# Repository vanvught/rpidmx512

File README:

Raspberry Pi DMX512 / RDM / MIMI / OSC / ArtNet-3 / Pixel
=======

*. RDM Controller with USB [Compatible with Enttec USB Pro protocol], 

*. ArtNet 3 DMX Node / Pixel (WS28xx) controller
*. WiFi ArtNet 3 DMX Node / Pixel (WS28xx) controller

*. RDM Responder 
*. Logic RDM Sniffer,

*. MIDI Sniffer,
*. MIDI-DMX Bridge

*. OSC-SPI (WS28xx) Bridge

Detailed information can be found here : http://www.raspberrypi-dmx.com/

Special thanks to @rsta2 (Rene Stange), who helped me get the multi-core support working.
https://github.com/rsta2/circle

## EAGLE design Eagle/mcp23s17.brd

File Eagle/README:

DMX512/RDM
=======

DMX512/RDM controller for Raspberry Pi

Detailed information can be found here : http://www.raspberrypi-dmx.com/

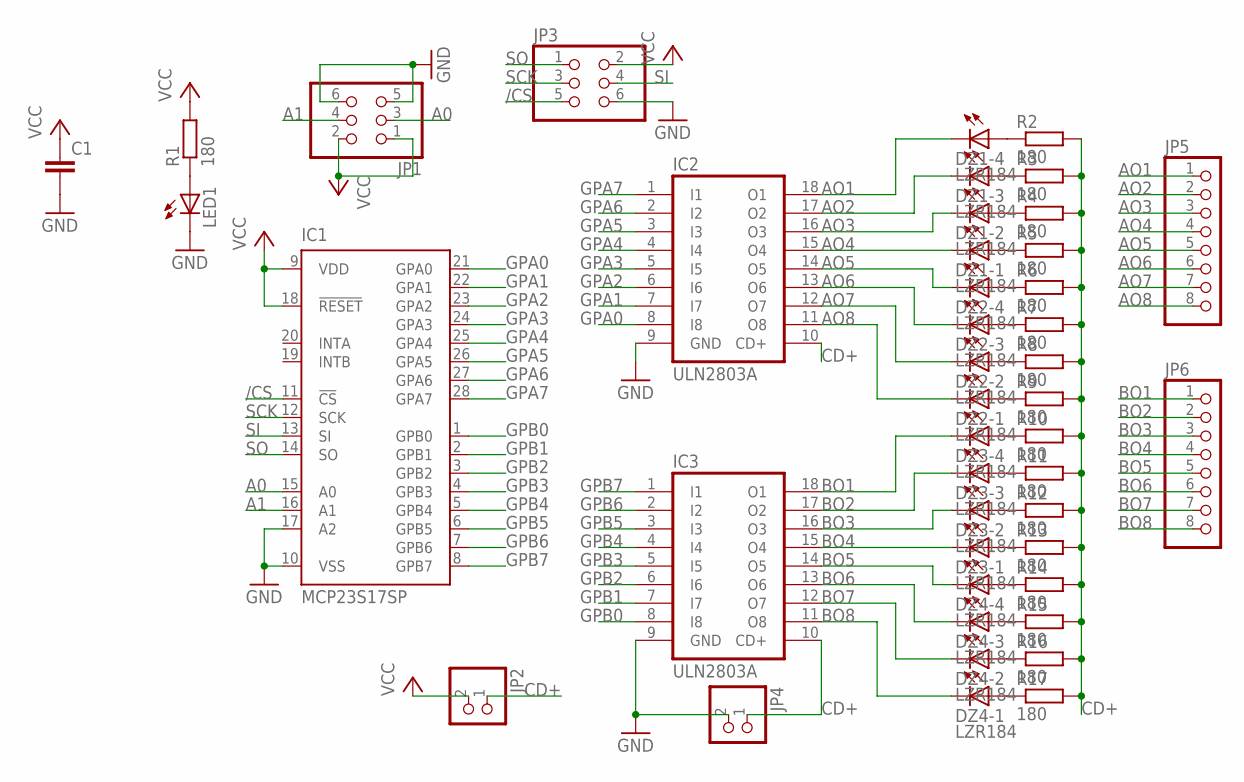
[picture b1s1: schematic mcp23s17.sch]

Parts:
C1: C-EU050-024X044; C050-024X044
DZ1, DZ2, DZ3, DZ4: LZR184
IC1: MCP23S17SP; DIL28-3
IC2, IC3: ULN2803A; DIL18
JP1, JP3: PINHD-2X3; 2X03
JP2, JP4: PINHD-1X2; 1X02
JP5, JP6: PINHD-1X8; 1X08
LED1: LED3MM
R1, R2, R3, R4, R5, R6, R7, R8, R9, R10, R11, R12, R13, R14, R15, R16, R17: 180; 0204V

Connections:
/CS: IC1.11 (!CS), JP3.5
A0: IC1.15 (A0), JP1.3
A1: IC1.16 (A1), JP1.4
AO1: DZ1.K4 (C), IC2.18 (O1), JP5.1
AO2: DZ1.K3 (C), IC2.17 (O2), JP5.2
AO3: DZ1.K2 (C), IC2.16 (O3), JP5.3
AO4: DZ1.K1 (C), IC2.15 (O4), JP5.4
AO5: DZ2.K4 (C), IC2.14 (O5), JP5.5
AO6: DZ2.K3 (C), IC2.13 (O6), JP5.6
AO7: DZ2.K2 (C), IC2.12 (O7), JP5.7
AO8: DZ2.K1 (C), IC2.11 (O8), JP5.8
BO1: DZ3.K4 (C), IC3.18 (O1), JP6.1
BO2: DZ3.K3 (C), IC3.17 (O2), JP6.2
BO3: DZ3.K2 (C), IC3.16 (O3), JP6.3
BO4: DZ3.K1 (C), IC3.15 (O4), JP6.4
BO5: DZ4.K4 (C), IC3.14 (O5), JP6.5
BO6: DZ4.K3 (C), IC3.13 (O6), JP6.6
BO7: DZ4.K2 (C), IC3.12 (O7), JP6.7
BO8: DZ4.K1 (C), IC3.11 (O8), JP6.8
CD+: IC2.10 (CD+), IC3.10 (CD+), JP2.1, JP4.1, R2.2, R3.2, R4.2, R5.2, R6.2, R7.2, R8.2, R9.2, R10.2, R11.2, R12.2, R13.2, R14.2, R15.2, R16.2, R17.2
GND: C1.2, IC1.10 (VSS), IC1.17 (A2), IC2.9 (GND), IC3.9 (GND), JP1.5, JP1.6, JP3.6, JP4.2, LED1.K (C)
GPA0: IC1.21 (GPA0), IC2.8 (I8)
GPA1: IC1.22 (GPA1), IC2.7 (I7)
GPA2: IC1.23 (GPA2), IC2.6 (I6)
GPA3: IC1.24 (GPA3), IC2.5 (I5)
GPA4: IC1.25 (GPA4), IC2.4 (I4)
GPA5: IC1.26 (GPA5), IC2.3 (I3)
GPA6: IC1.27 (GPA6), IC2.2 (I2)
GPA7: IC1.28 (GPA7), IC2.1 (I1)
GPB0: IC1.1 (GPB0), IC3.8 (I8)
GPB1: IC1.2 (GPB1), IC3.7 (I7)
GPB2: IC1.3 (GPB2), IC3.6 (I6)
GPB3: IC1.4 (GPB3), IC3.5 (I5)
GPB4: IC1.5 (GPB4), IC3.4 (I4)
GPB5: IC1.6 (GPB5), IC3.3 (I3)
GPB6: IC1.7 (GPB6), IC3.2 (I2)
GPB7: IC1.8 (GPB7), IC3.1 (I1)
unnamed: LED1.A, R1.1
unnamed: DZ3.A4 (A), R10.1
unnamed: DZ3.A3 (A), R11.1
unnamed: DZ3.A2 (A), R12.1
unnamed: DZ3.A1 (A), R13.1
unnamed: DZ4.A4 (A), R14.1
unnamed: DZ4.A3 (A), R15.1
unnamed: DZ4.A2 (A), R16.1
unnamed: DZ4.A1 (A), R17.1
unnamed: DZ1.A4 (A), R2.1
unnamed: DZ1.A3 (A), R3.1
unnamed: DZ1.A2 (A), R4.1
unnamed: DZ1.A1 (A), R5.1
unnamed: DZ2.A4 (A), R6.1
unnamed: DZ2.A3 (A), R7.1
unnamed: DZ2.A2 (A), R8.1
unnamed: DZ2.A1 (A), R9.1
SCK: IC1.12 (SCK), JP3.3
SI: IC1.13 (SI), JP3.4
SO: IC1.14 (SO), JP3.1
VCC: C1.1, IC1.9 (VDD), IC1.18 (!RESET), JP1.1, JP1.2, JP2.2, JP3.2, R1.2

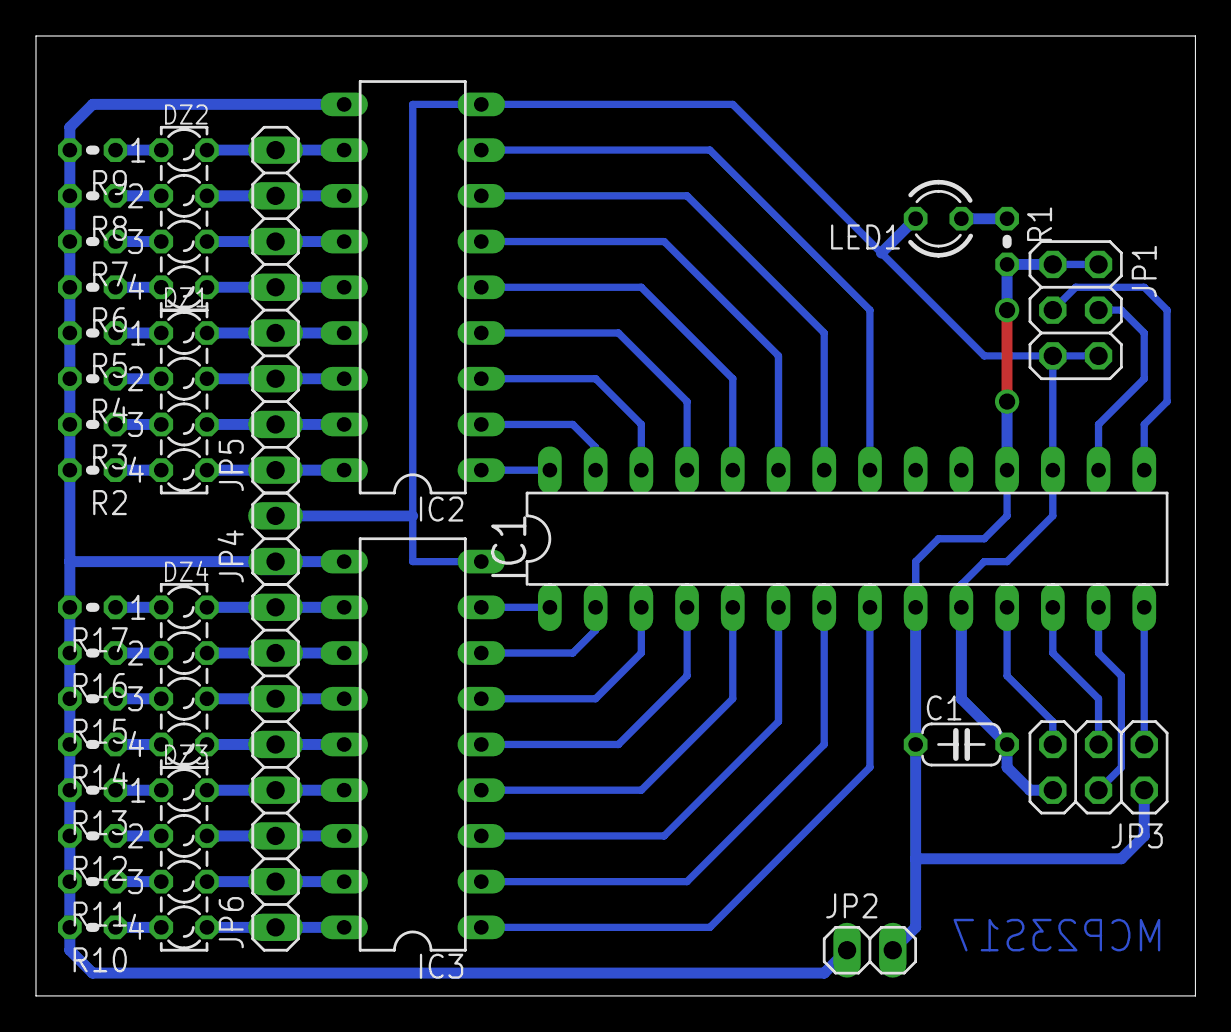
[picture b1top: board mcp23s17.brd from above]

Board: 2 copper layers, 64.4 x 53.3 mm, 32 parts (0 on the bottom side), 58 nets.

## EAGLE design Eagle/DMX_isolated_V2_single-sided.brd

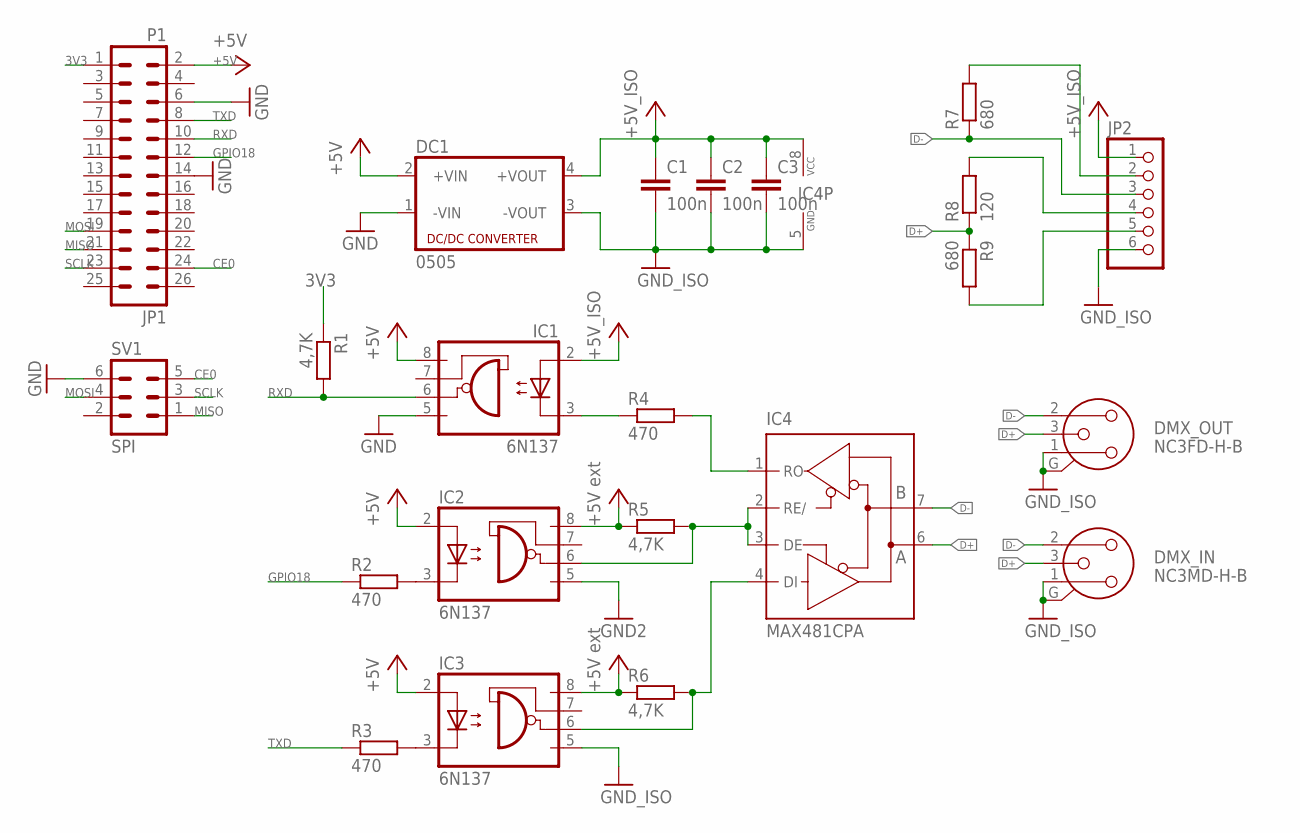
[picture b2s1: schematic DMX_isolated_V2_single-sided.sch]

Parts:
C1, C2, C3: 100n; C050-024X044
DC1: 0505; NME
DMX_IN: NC3MD-H-B
DMX_OUT: NC3FD-H-B
IC1, IC2, IC3: 6N137; DIL08
IC4: MAX481CPA; DIL08
JP1: P1; MA13-2
JP2: PINHD-1X6; 1X06
R1, R5, R6: 4,7K; 0204V
R2, R3, R4: 470; 0204V
R7, R9: 680; 0204V
R8: 120; 0204V
SV1: SPI; MA03-2

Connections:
3V3: JP1.1, R1.1
+5V: DC1.2 (+VIN), IC1.8 (VCC), IC2.2 (A), IC3.2 (A), JP1.2
+5V_ISO: C1.1, C2.1, C3.1, DC1.4 (+VOUT), IC1.2 (A), IC2.8 (VCC), IC3.8 (VCC), IC4.8 (VCC), JP2.1, R5.1, R6.1
CE0: JP1.24, SV1.5
D+: DMX_IN.3, DMX_OUT.3, IC4.6 (A), R8.1, R9.1
D-: DMX_IN.2 (1), DMX_OUT.2 (1), IC4.7 (B), JP2.3, R7.1
GND: DC1.1 (-VIN), IC1.5 (GND), JP1.6, JP1.14, SV1.6
GND_ISO: C1.2, C2.2, C3.2, DC1.3 (-VOUT), DMX_IN.1 (2), DMX_IN.G, DMX_OUT.1 (2), DMX_OUT.G, IC2.5 (GND), IC3.5 (GND), IC4.5 (GND), JP2.6
GPIO18: JP1.12, R2.1
MISO: JP1.21, SV1.1
MOSI: JP1.19, SV1.4
unnamed: JP2.5, R9.2
unnamed: IC2.3 (C), R2.2
unnamed: IC2.6 (VO), IC4.2 (RE/), IC4.3 (DE), R5.2
unnamed: IC3.3 (C), R3.2
unnamed: IC3.6 (VO), IC4.4 (DI), R6.2
unnamed: IC1.3 (C), R4.1
unnamed: IC4.1 (RO), R4.2
unnamed: JP2.4, R8.2
unnamed: JP2.2, R7.2
RXD: IC1.6 (VO), JP1.10, R1.2
SCLK: JP1.23, SV1.3
TXD: JP1.8, R3.1

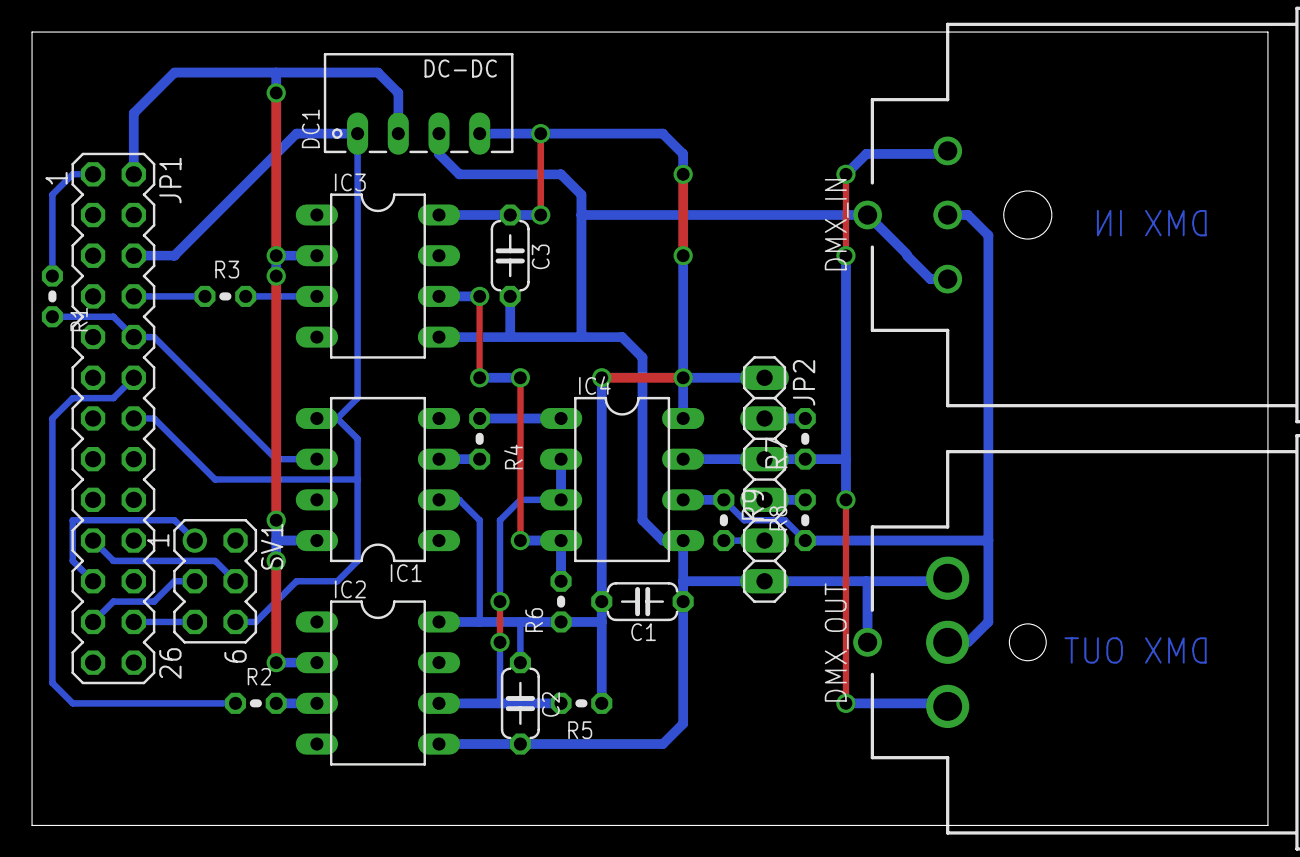
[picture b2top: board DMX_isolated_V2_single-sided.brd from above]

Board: 2 copper layers, 77.1 x 49.5 mm, 22 parts (0 on the bottom side), 23 nets.

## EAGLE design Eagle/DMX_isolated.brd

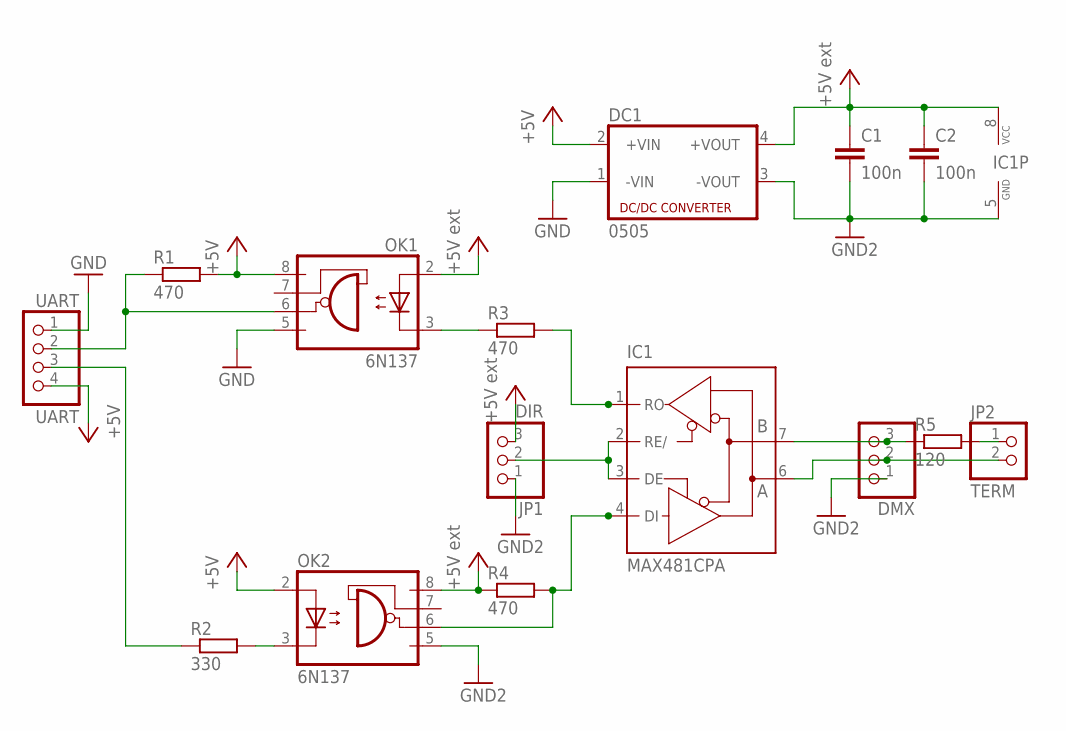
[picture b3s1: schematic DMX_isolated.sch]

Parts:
C1, C2: 100n; C050-024X044
DC1: 0505; NME
DMX: 1X03
IC1: MAX481CPA; DIL08
JP1: DIR; 1X03
JP2: TERM; 1X02
OK1, OK2: 6N137; DIL08
R1, R3: 470; 0204/5
R2: 330; 0204/5
R4: 470; 0204V
R5: 120; 0204V
UART: UART; 1X04

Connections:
+5V: DC1.2 (+VIN), OK1.8 (VCC), OK2.2 (A), R1.2, UART.4
+5V_EXT: C1.1, C2.1, DC1.4 (+VOUT), IC1.8 (VCC), JP1.3, OK1.2 (A), OK2.8 (VCC), R4.1
D2: R2.1, UART.3
GND: DC1.1 (-VIN), OK1.5 (GND), UART.1
GND_EXT: C1.2, C2.2, DC1.3 (-VOUT), DMX.1, IC1.5 (GND), JP1.1, OK2.5 (GND)
unnamed: JP2.1, R5.2
unnamed: DMX.3, IC1.7 (B), R5.1
unnamed: OK2.3 (C), R2.2
unnamed: IC1.2 (RE/), IC1.3 (DE), JP1.2
unnamed: IC1.4 (DI), OK2.6 (VO), R4.2
unnamed: OK1.3 (C), R3.1
unnamed: IC1.1 (RO), R3.2
unnamed: OK1.6 (VO), R1.1, UART.2
unnamed: DMX.2, IC1.6 (A), JP2.2

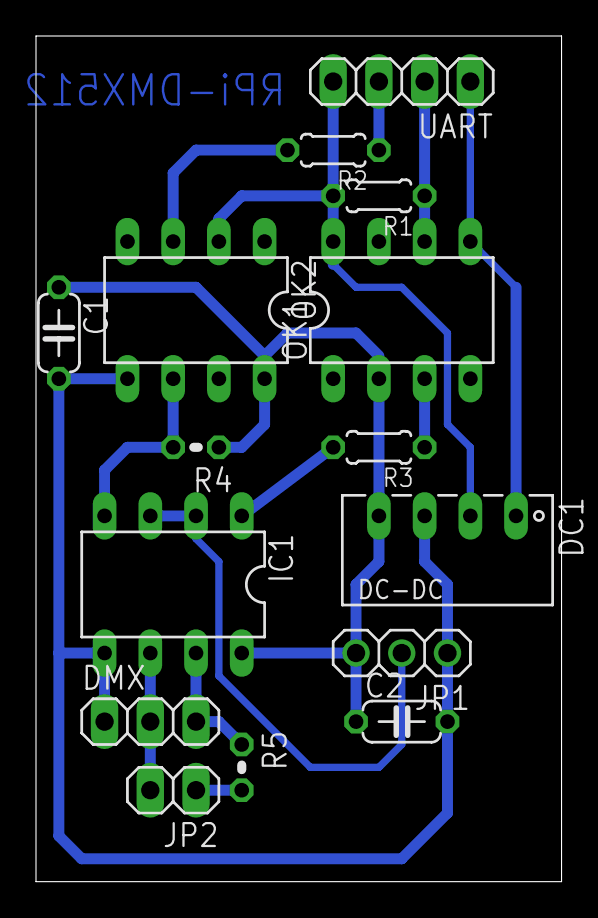
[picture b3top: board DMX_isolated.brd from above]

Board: 2 copper layers, 29.2 x 47.0 mm, 15 parts (0 on the bottom side), 14 nets.

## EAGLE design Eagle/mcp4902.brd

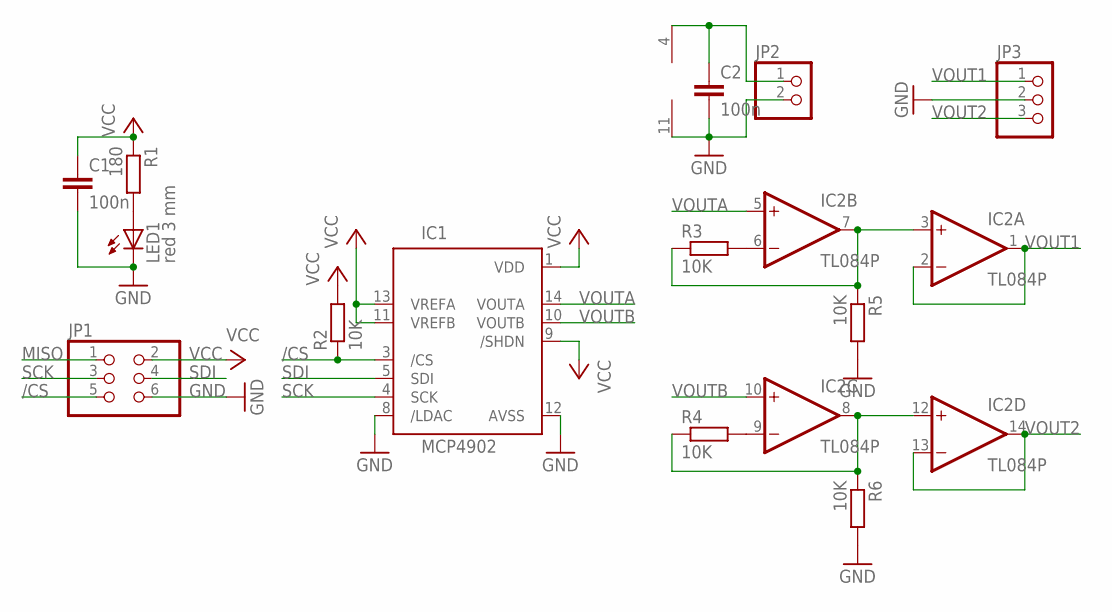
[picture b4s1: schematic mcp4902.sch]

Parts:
C1, C2: 100n; C050-024X044
IC1: MCP4902; DIL14
IC2: TL084P; DIL14
JP1: PINHD-2X3; 2X03
JP2: PINHD-1X2; 1X02
JP3: PINHD-1X3; 1X03
LED1: red 3 mm; LED3MM
R1: 180; 0204V
R2, R3, R4, R5, R6: 10K; 0204V

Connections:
/CS: IC1.3 (/CS), JP1.5, R2.1
GND: C1.2, C2.2, IC1.8 (/LDAC), IC1.12 (AVSS), IC2.11 (V-), JP1.6, JP2.2, JP3.2, LED1.K (C), R5.2, R6.2
MISO: JP1.1
unnamed: LED1.A, R1.2
unnamed: IC2.6 (-IN), R3.2
unnamed: IC2.9 (-IN), R4.2
unnamed: IC2.3 (+IN), IC2.7 (OUT), R3.1, R5.1
unnamed: IC2.8 (OUT), IC2.12 (+IN), R4.1, R6.1
SCK: IC1.4 (SCK), JP1.3
SDI: IC1.5 (SDI), JP1.4
V+: C2.1, IC2.4 (V+), JP2.1
VCC: C1.1, IC1.1 (VDD), IC1.9 (/SHDN), IC1.11 (VREFB), IC1.13 (VREFA), JP1.2, R1.1, R2.2
VOUT1: IC2.1 (OUT), IC2.2 (-IN), JP3.1
VOUT2: IC2.13 (-IN), IC2.14 (OUT), JP3.3
VOUTA: IC1.14 (VOUTA), IC2.5 (+IN)
VOUTB: IC1.10 (VOUTB), IC2.10 (+IN)

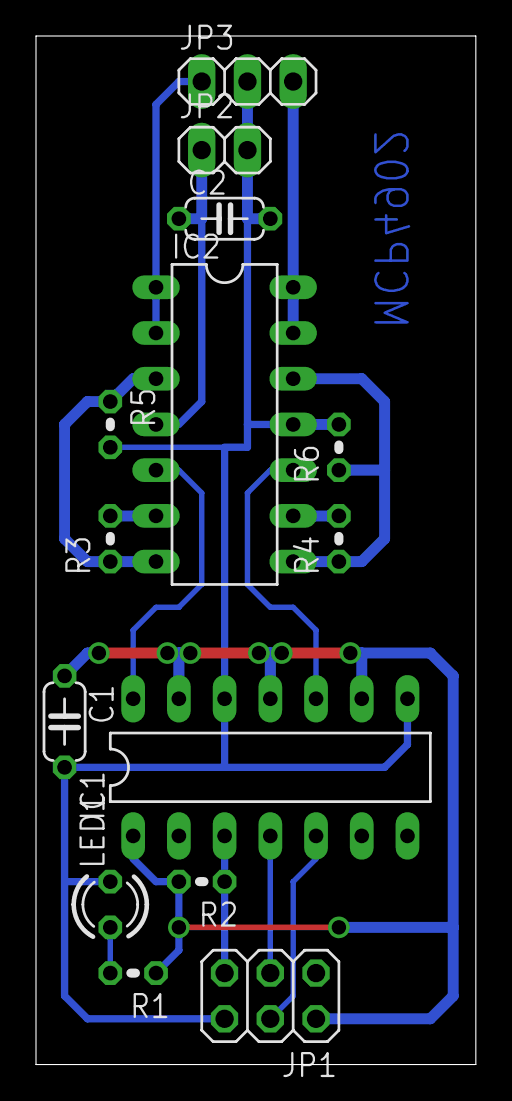
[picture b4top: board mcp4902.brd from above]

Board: 2 copper layers, 24.4 x 57.1 mm, 14 parts (0 on the bottom side), 15 nets.

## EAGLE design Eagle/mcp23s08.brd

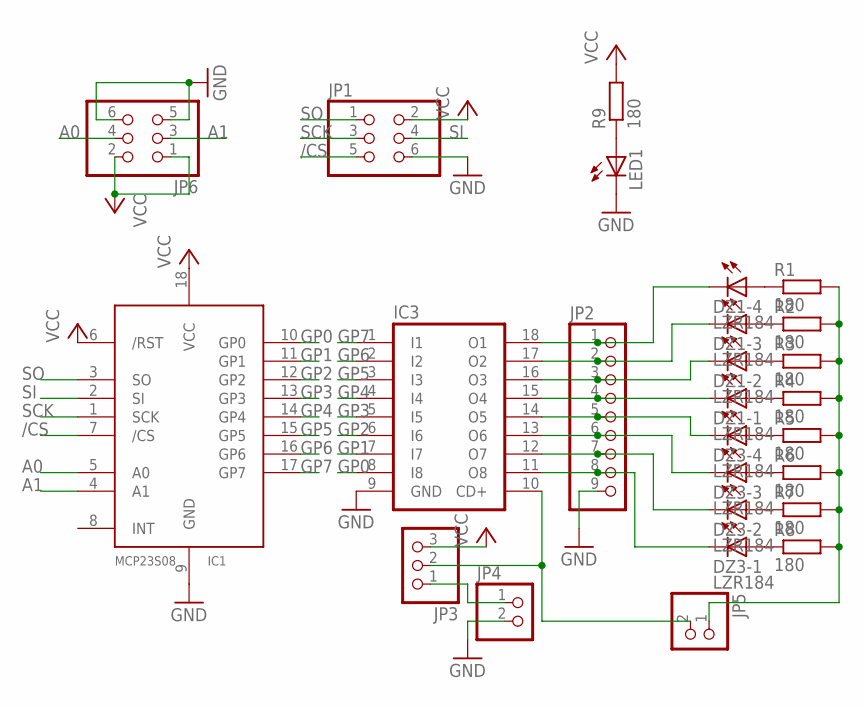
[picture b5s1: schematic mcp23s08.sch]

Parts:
DZ1, DZ3: LZR184
IC1: MCP2300X/P; DIL18
IC3: ULN2803A; DIL18
JP1, JP6: PINHD-2X3; 2X03
JP2: PINHD-1X9; 1X09
JP3: PINHD-1X3; 1X03
JP4, JP5: PINHD-1X2; 1X02
LED1: LED3MM
R1, R2, R3, R4, R5, R6, R7, R8, R9: 180; 0204V

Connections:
/CS: IC1.7 (/CS), JP1.5
A0: IC1.5 (A0), JP6.4
A1: IC1.4 (A1), JP6.3
GND: IC1.9 (GND), IC3.9 (GND), JP1.6, JP2.9, JP4.2, JP6.5, JP6.6, LED1.K (C)
GP0: IC1.10 (GP0), IC3.8 (I8)
GP1: IC1.11 (GP1), IC3.7 (I7)
GP2: IC1.12 (GP2), IC3.6 (I6)
GP3: IC1.13 (GP3), IC3.5 (I5)
GP4: IC1.14 (GP4), IC3.4 (I4)
GP5: IC1.15 (GP5), IC3.3 (I3)
GP6: IC1.16 (GP6), IC3.2 (I2)
GP7: IC1.17 (GP7), IC3.1 (I1)
unnamed: JP5.1, R1.2, R2.2, R3.2, R4.2, R5.2, R6.2, R7.2, R8.2
unnamed: LED1.A, R9.1
unnamed: DZ1.K4 (C), IC3.18 (O1), JP2.1
unnamed: DZ1.K3 (C), IC3.17 (O2), JP2.2
unnamed: DZ1.K2 (C), IC3.16 (O3), JP2.3
unnamed: DZ1.K1 (C), IC3.15 (O4), JP2.4
unnamed: DZ3.K4 (C), IC3.14 (O5), JP2.5
unnamed: DZ3.K3 (C), IC3.13 (O6), JP2.6
unnamed: DZ3.K2 (C), IC3.12 (O7), JP2.7
unnamed: DZ3.K1 (C), IC3.11 (O8), JP2.8
unnamed: JP3.1, JP4.1
unnamed: IC3.10 (CD+), JP3.2, JP5.2
unnamed: DZ1.A4 (A), R1.1
unnamed: DZ1.A3 (A), R2.1
unnamed: DZ1.A2 (A), R3.1
unnamed: DZ1.A1 (A), R4.1
unnamed: DZ3.A4 (A), R5.1
unnamed: DZ3.A3 (A), R6.1
unnamed: DZ3.A2 (A), R7.1
unnamed: DZ3.A1 (A), R8.1
SCK: IC1.1 (SCK), JP1.3
SI: IC1.2 (SI), JP1.4
SO: IC1.3 (SO), JP1.1
VCC: IC1.6 (/RST), IC1.18 (VCC), JP1.2, JP3.3, JP6.1, JP6.2, R9.2

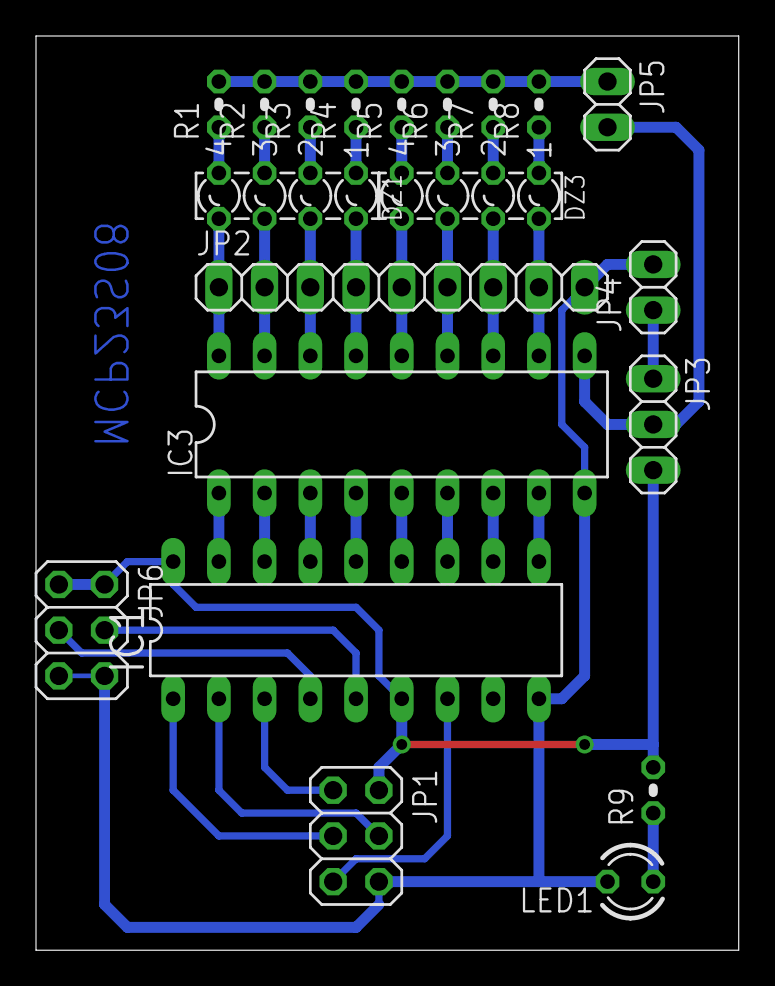
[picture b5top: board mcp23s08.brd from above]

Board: 2 copper layers, 39.0 x 50.8 mm, 20 parts (0 on the bottom side), 36 nets.

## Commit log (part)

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2024-12-27 Updated SOFTWARE_VERSION[]
2025-01-10 Minor refactoring
    - Added IPADDR_LOOPBACK
    - Added void tcp_abort(const int32_t nHandleListen, const uint32_t nHandleConnection)
2025-01-10 Refactoring
2025-01-26 The ConfigStore::Flash is now based on the Software Timer
2025-02-07 Minor cleanup
2026-01-04 Refactor and modularize codebase structure
    * Major project restructuring
    * Reorganized libraries and source files into a clearer, more modular directory structure.
    * Moved, renamed, or removed numerous files to reduce duplication and improve maintainability.
    * Legacy code cleanup
    * Removed deprecated and unused code from lib-lightset, lib-network, lib-properties, and older display components.
    * Eliminated redundant parameter and platform-specific files no longer in use.
2026-01-16 Refactor mDNS and network naming, update NTP/OSC usage
    Replaces direct mdns namespace usage with network::apps::mdns and updates service enum names to k-prefixed style across AppleMIDI, OSC, NTP, and PixelPusher code. Refactors NTP packet field names to 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
2026-02-06 Add do-tftp and udp_send scripts plus gd32 README
    Introduce two new Python tools and a brief README link:
    - common/scripts/udp_send.py: UDP helper matching the original C behavior (binds local port 10501, sends up to 512 bytes, and waits up to 1s for a reply when the payload starts with '?'). Exposes sen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
    - common/scripts/do-tftp.py: Python port of the provided bash orchestration script. Uses udp_send.py to control a device (toggle TFTP on/off, wait for status, reboot, and run the system 'tftp' client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
    - common/s
2026-02-24 Refactor: naming, style, headers and minor fixes
    Apply broad code cleanup and refactoring across the LTC and SMPTE projects:
    - Update copyright years to 2026 in multiple files.
    - Add IWYU pragma comments and tidy header includes/guards.
    - Modernize naming and style: convert many identifiers to snake_case or k-prefixed constants, unify enum/value names, and adjust spacing/braces.
    - Refactor classes and APIs: DisplayEditFps/DisplayEditTimeCode (cursor and state naming, helper methods), McpButtons (constructor args, members, constants, button handling and LED logic), LtcOscServ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
2026-02-27 Disable RDM BgDiscovery and cleanup headers
    Comment out the Art-Net RDM BgDiscovery JSON emission (marked "Will implement on request") to defer implementing background discovery. Also apply whitespace and style cleanups in configurationstore.h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
2026-03-01 Use nullptr instead of null in header
    Replace the non-standard 'null' initializer with C++11 'nullptr' for ArtNetRdmResponder pointer in lib-artnet/include/artnetnode.h to improve type safety and avoid potential compilation issues.
2026-03-05 Refactor RDM discovery & ArtNet output handling
    Rename RestartOutputPort to StopOutputPort and centralize output stop logic; StopOutputPort now clears is_transmitting and stops DMX. Refactor ArtNet::HandleDmx: reorder and simplify merge-case branc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
2026-03-08 Remove prefetch pragma and update copyrights
    Remove -fprefetch-loop-arrays GCC pragmas across multiple sources, bump copyright years to 2026 in several headers/sources, and apply small formatting/whitespace cleanups (include spacing, end-of-ifd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
    Also: add NODE_RDMNET_LLRP_ONLY include handling to several Rules.mk (lib-displayudf, lib-pixeldmx, lib-showfile), minor code tweaks such as renaming a local variable (type -> kType), collapsing Sync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
2026-03-18 Update DMX config storage & move DHCP flag
    Rename and consolidate DMX config storage, remove personality field/key, and relocate Art-Net DHCP status handling.
    - DMX: renamed static store from store_dmxnode_ to store_dmxnode and updated all references; removed 'personality' field and JSON key/handler from DmxNodeParamsConst and DmxNodeParams, adjusted Confi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
    - Art-Net: moved network::iface::Dhcp() status update into SendPollReply (removed redundant updates from Start() and HandleIpProg) and removed an unused include in artnetparams.cpp.
    These changes simplify the
2026-03-24 Enforce RFC1123 hostnames; update prefixes
    Bump copyright year to 2026, add RFC1123 comment describing valid hostname rules, and replace underscores with hyphens in HOST_NAME_PREFIX values (e.g. "allwinner_" -> "allwinner-", "gigadevice_" -> 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
2026-03-28 Remove ENABLE_CONTENT flag and update HTTPD checks
    Remove the ENABLE_CONTENT define from multiple target Makefiles and update code to rely on ENABLE_HTTPD only. Adjust conditional compilation in lib-artnet (artnetcontroller.cpp, artnetnode.cpp) to ch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
2026-04-06 Use artnet UDP API for timecode
    Replace the previous ArtNetNode dependency with a lightweight artnet UDP API: add artnet::SendTimeCode, parse incoming ArtTimeCode UDP packets in ArtNetReader, and use network::udp begin/end/send for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
2026-04-06 Implement strnlen and reformat string headers
    Add strnlen implementation to include/string.h and expose it in include/cstring; reformat and normalize function declarations/implementations (added NOLINT comments, adjusted brace/indent style) and 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
2026-04-11 Format headers and update copyrights
    Apply widespread style and formatting changes to lib-network header files: convert namespace blocks to single-line declarations, compact enums/structs and small unions, collapse short functions into 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
2026-04-15 Use template literals and add form handler
    Replace concatenated HTML with a template literal for the DMX monitor card, add accept-charset on the form, and attach a submit event listener via addEventListener (preventDefault + call dmxmonitor.s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
2026-04-17 Use s_if_name and refactor network Linux code
    Replace uses of m_aIfName with the canonical s_if_name in network.cpp to ensure the correct interface name is used. Clean up and reformat Linux/macOS network source files: tidy bracing/spacing, adjus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
2026-04-22 Use emac::link::StatusRead in network.h
    Fix incorrect namespace qualifier in lib-network/include/emac/network.h by replacing net::link::StatusRead() with emac::link::StatusRead(). This ensures the correct function is called when polling PH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
2026-04-23 Rename nDmxStartAddress to dmx_start_address
    Replace the Hungarian-style parameter/local name nDmxStartAddress with snake_case dmx_start_address across multiple modules for consistency and readability. Updates touch displayudf, dmxmonitor, l647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
2026-04-23 Refactor GPS code and platform GPIO API
    Apply style and API cleanups across the lib-gps module: update copyright years to 2026, normalize brace/indent/style, and compact enums/arrays (e.g. aTag -> kTag). Rename platform GPIO functions to P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
2026-04-28 Fix @file tags to network_*.h
    Update header comment @file tags to match actual filenames for consistency and clarity: changed 'net_memcpy.h' to 'network_memcpy.h' in network_memcpy.h and 'net_private.h' to 'network_private.h' in 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
2026-05-01 Introduce Bit helper; fix port_index_ in LED calls
    Replace ad-hoc (1U << port) bit operations with a centralized Bit(index) constexpr and proper uint8_t casts to improve readability and correctness. Update kPorts reference to dmx::config::max::kPorts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
2026-05-04 Use UINT32_MAX instead of ~0 casts
    Replace various uses of static_cast<uint32_t>(~0) (and similar bitwise inversions) with the explicit UINT32_MAX constant for clarity and portability. Changes span: lib-device (MCP3424 error/return va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
2026-05-04 Refactor naming and formatting in lib-rdm
    Rename variables for clarity and consistency, normalize brace/whitespace style, and update copyright years. Key changes: kCommandClass/kParamId replace nCommandClass/nParamId; is_rdm/is_rdm_net repla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
2026-05-07 Rename DMX/RDM APIs to Transmit/Direction
    Refactor DMX/RDM public APIs for clarity and consistency in lib-dmx include headers (h3/multi/dmx.h and h3/single/dmx.h).
    - Replace dmx::PortDirection with dmx::Direction and rename getter GetPortDirection -> PortDirection
    - Rename DMX transmit-related APIs: SetDmxBreakTime/GetDmxBreakTime -> SetTransmitBreakTime/TransmitBreakTime (and similarly for MAB, Period, Slots)
    - Rename send templates: SetSendData* -> SetTransmitDataWithSC / SetTransmitDataWithoutSC and update inline template name
    - Rename RDM send APIs to RdmTransmit / RdmTransmitDiscoveryRespondMessage and add RDM receive declarations
    - Update port_direction_ member type to dmx::Direction
2026-05-20 Replace hal watchdog API with watchdog:: interface
    Migrate multiple firmware main.cpp files from the legacy hal watchdog to the new watchdog module: replace h3/gd32 hal_watchdog includes with "watchdog.h" and update hal::WatchdogInit()/WatchdogFeed()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
2026-05-21 Use kPixelType.name in Dump() output
    Replace LtcDisplayParamsConst::kPixelType with LtcDisplayParamsConst::kPixelType.name in the Dump() printf call so the pixel type's name field is printed. This aligns the line with the other paramete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
2026-05-29 Add PixelTestPattern instances and debug logs
    Introduce local PixelTestPattern instances across firmware apps and update Show API to accept an explicit pattern. Pass test pattern states into Dmx/Display setup and use instance-based GetPattern() 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
2026-06-03 Add gzip support for embedded content
    Introduce optional gzip compression for generated embedded assets. Define USE_GZIP by default (unless overridden) and add ConvertToHCompressed() which pipes files through gzip to produce a uint8_t C 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
2026-06-04 Refactor UUID headers and UuidCopy usage
    Replace hal-specific UUID header and namespace with a unified uuid.h API, move/rename H3 UUID sources, and add a Linux uuid header. Files now include "uuid.h" instead of "hal_uuid.h" and calls to hal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
2026-06-06 Add firmware upload UI and backend integration
    Introduce a firmware upload feature and wire it into the HTTP content pipeline. Changes include:
    - Add preprocessor feature guard for uploads in generate_content.cpp so upload assets are conditionally included.
    - Register /upload route in khtmlinfos.cpp to serve upload/index.html.
    - Add a modern upload page JS (modern/upload_index.js) implementing chunked uploads, abort/cancel, progress bar, drag-and-drop, metadata display and logging.
    - Add compressed upload_index.js.h with the upload page payload.
    - Add upload-specific styles in styles.css for file input, drop zone, progress bar and log output.
2026-06-11 Replace HAL_I2C with i2c API and modernize sensors
    Refactor device sensor drivers to use the new i2c interface instead of inheriting HAL_I2C: remove HAL_I2C base classes, add address_/initialized_ members, and replace HAL_I2C calls with i2c:: functio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
2026-06-11 Reorder PixelTestPattern
    Include firmware/debug/debug_debug.h and move the PixelTestPattern instantiation to after PixelDmxMulti in main.cpp. This adjusts initialization ordering (ensuring PixelDmxMulti is constructed before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
2026-06-12 Unify SPI API and refactor drivers
    Introduce a unified SPI wrapper and migrate drivers to it. Adds a Spi helper class (lib-h3/include/spi.h) and replaces direct hal_spi/hal wrapper usage with spi.h calls (spi::Begin, spi::Write, spi::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
2026-06-15 Implement Linux I2C backend; remove linux_i2c.h
    Provide a native Linux implementation for i2c: open /dev/i2c-1, manage a file descriptor, set slave address via ioctl(I2C_SLAVE), and perform reads/writes using POSIX read/write with error handling (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
2026-06-15 Detect board via device-tree and add platform defines
    Replace vcgencmd-based Raspberry Pi detection and bcm2835-specific logic with device-tree model probing. The Makefile now adds -DLINUX, reads /sys/firmware/devicetree/base/model into DT_MODEL (printe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
2026-06-16 Use GPIO_FSEL_* and static_cast for masks
    Replace usages of gpio::Select::kOutput/kInput with GPIO_FSEL_OUTPUT/INPUT and convert C-style (uint32_t) casts to static_cast<uint32_t> for mask operations in lib-usb/src/h3/ft245rl.cpp. Changes tou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
2026-06-18 Reformat json_config_rdmsensors.cpp
    Update file formatting and copyright year. The copyright notice was extended to 2025-2026 and the namespace/function brace placement and indentation were reformatted. No functional or logic changes w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
2026-06-19 Add Odroid GPIO support and safety checks
    Add gpio_odroid.h with GPIO_EXT_* mappings for Odroid and include it in SPI config to set reset/DC/BL/CS pins when ODROID is defined. Add bounds checks in lib-linux gpio functions (Set, Clr, Lev) to 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
2026-06-28 Tidy debug_dump style and no-op linkage
    Normalize brace/loop formatting in `debug_dump.h` to match project style, and change the `NDEBUG` no-op `Dump` to `static inline` for internal linkage in release builds.
